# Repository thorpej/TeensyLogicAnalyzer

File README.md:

# TeensyLogicAnalyzer
Simple logic analyzer for 8-bit CPUs based on Jeff Tranter's 8-bit CPU logic analyzer

This is a work-in-progress.  You can find Jeff's work [here](https://github.com/jefftranter/6502).

This version aims to support a wide variety of 8-bit CPUs (so long as they fit in a 40-pin DIP)
and be easily expandable to new CPU types (e.g. 8080 and 8088) through the use of off-board adapter
modules, as well as to support sampling the full complement of control signals on the supported CPUs.

The main board is very similar to Jeff's original: it contains the Teensy 4.1, input buffers to
level-shift the 5V TTL signals from the target CPU down to the 3.3V levels supported by the Teensy,
a manual trigger button, and a ground reference pin (as a convenience).

The main difference is the use of a single keyed 40-pin IDC header.  This header's pinout does not
correspond directly to any single CPU type, but merely provides the input to the analyzer.
Individual adapter modules mate the analyzer to a specific CPU.  These adapter modules also contain
a 40-pin keyed IDC header, as well as 2 (optionally 3) rows of 1x20 pin headers for connecting a 40-pin
DIP clip to the adapter.  The adapter maps the target CPU's pin configuration to the analyzer's input
pins.  In addition to providing future expandability, it also keeps the manufacturing cost of the boards
low (some PCB fabricators charge as little as $5 + shipping for a run of 10 if the board is smaller
than 100mm x 100mm).  The analyzer board is approximately 91mm x 91mm (roughly 3.5 inches square), and
uses all through-hole components to make it easy to build.

In addition, I plan to make some specific enhancements to the 6809 support, including:
- Support additional signals on the 6809 (e.g. BS, BA, /FIRQ, /HALT).
- Properly notice instruction fetch on 6809E (by watching the LIC signal).
- Improve 6809 dissasembly (decode all of the addressing modes, as well as the 2-byte opcodes).

Beause the 6809E enhancements I want to make require additional signals to be routed, I needed
to make a new board anyway, which is why this project exists.

More to come.  Stay tuned!

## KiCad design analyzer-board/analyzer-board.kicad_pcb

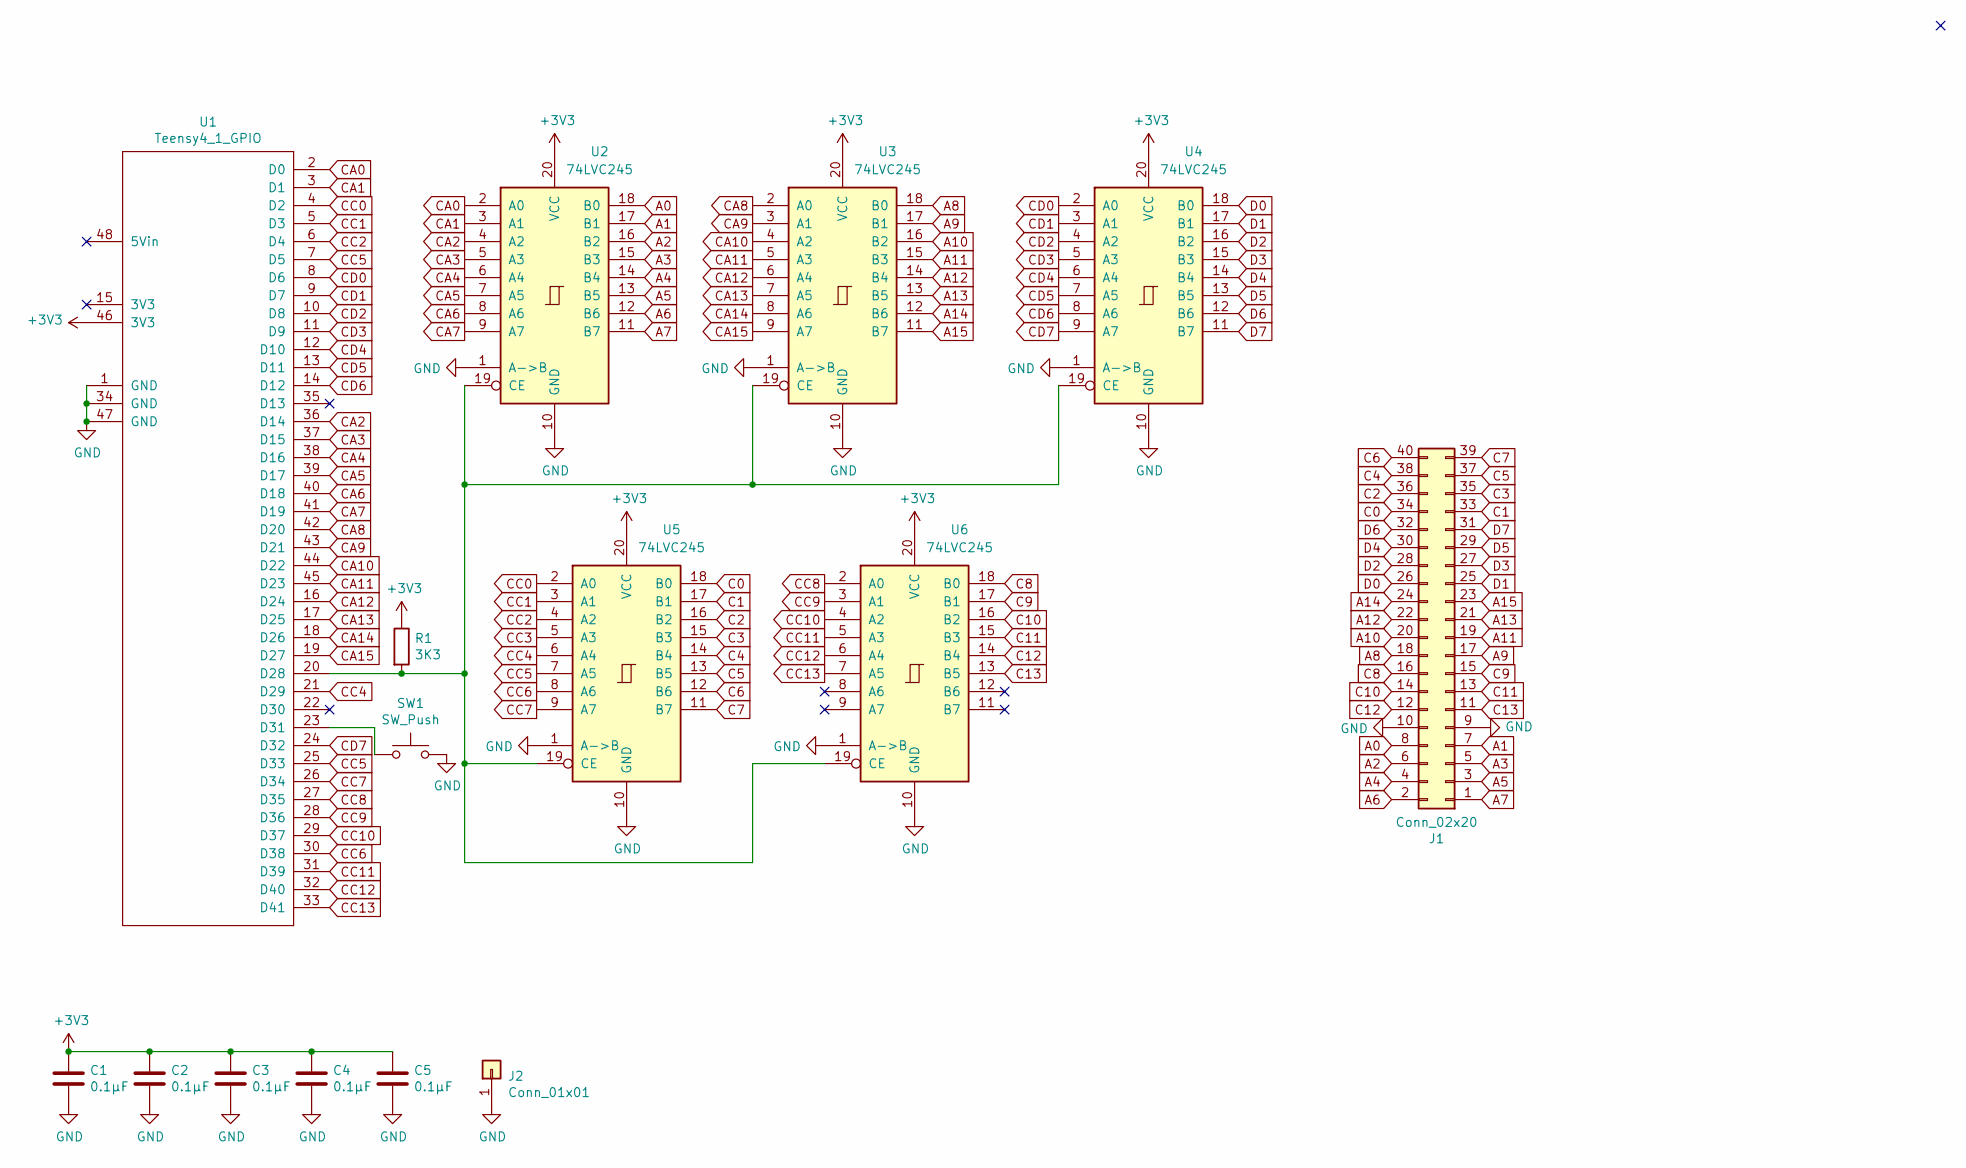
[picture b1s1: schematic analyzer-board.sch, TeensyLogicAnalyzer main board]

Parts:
C1, C2, C3, C4, C5: 0.1µF; C_Radial_D6.3mm_H5.0mm_P2.50mm; Mouser 80-C320C104K2R5TA
J1: Conn_02x20; PinHeader_2x20_P2.54mm_Vertical
J2: Conn_01x01; PinHeader_1x01_P2.54mm_Vertical
R1: 3K3; R_Axial_DIN0207_L6.3mm_D2.5mm_P7.62mm_Horizontal
SW1: SW_Push; SW_PUSH_6mm
U1: Teensy4_1_GPIO; DIP-48_W15.24mm_Socket
U2, U3, U4, U5, U6: 74LVC245; DIP-20_W7.62mm_Socket

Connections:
+3V3: C1.1, C2.1, C3.1, C4.1, C5.1, R1.1, U1.46 (3V3), U2.20 (VCC), U3.20 (VCC), U4.20 (VCC), U5.20 (VCC), U6.20 (VCC)
A0: J1.8, U2.18 (B0)
A1: J1.7, U2.17 (B1)
A2: J1.6, U2.16 (B2)
A3: J1.5, U2.15 (B3)
A4: J1.4, U2.14 (B4)
A5: J1.3, U2.13 (B5)
A6: J1.2, U2.12 (B6)
A7: J1.1, U2.11 (B7)
A8: J1.18, U3.18 (B0)
A9: J1.17, U3.17 (B1)
A10: J1.20, U3.16 (B2)
A11: J1.19, U3.15 (B3)
A12: J1.22, U3.14 (B4)
A13: J1.21, U3.13 (B5)
A14: J1.24, U3.12 (B6)
A15: J1.23, U3.11 (B7)
C0: J1.34, U5.18 (B0)
C1: J1.33, U5.17 (B1)
C2: J1.36, U5.16 (B2)
C3: J1.35, U5.15 (B3)
C4: J1.38, U5.14 (B4)
C5: J1.37, U5.13 (B5)
C6: J1.40, U5.12 (B6)
C7: J1.39, U5.11 (B7)
C8: J1.16, U6.18 (B0)
C9: J1.15, U6.17 (B1)
C10: J1.14, U6.16 (B2)
C11: J1.13, U6.15 (B3)
C12: J1.12, U6.14 (B4)
C13: J1.11, U6.13 (B5)
CA0: U1.2 (D0), U2.2 (A0)
CA1: U1.3 (D1), U2.3 (A1)
CA2: U1.36 (D14), U2.4 (A2)
CA3: U1.37 (D15), U2.5 (A3)
CA4: U1.38 (D16), U2.6 (A4)
CA5: U1.39 (D17), U2.7 (A5)
CA6: U1.40 (D18), U2.8 (A6)
CA7: U1.41 (D19), U2.9 (A7)
CA8: U1.42 (D20), U3.2 (A0)
CA9: U1.43 (D21), U3.3 (A1)
CA10: U1.44 (D22), U3.4 (A2)
CA11: U1.45 (D23), U3.5 (A3)
CA12: U1.16 (D24), U3.6 (A4)
CA13: U1.17 (D25), U3.7 (A5)
CA14: U1.18 (D26), U3.8 (A6)
CA15: U1.19 (D27), U3.9 (A7)
CC0: U1.4 (D2), U5.2 (A0)
CC1: U1.5 (D3), U5.3 (A1)
CC2: U1.6 (D4), U5.4 (A2)
CC3: U5.5 (A3)
CC4: U1.21 (D29), U5.6 (A4)
CC5: U1.7 (D5), U1.25 (D33), U5.7 (A5)
CC6: U1.30 (D38), U5.8 (A6)
CC7: U1.26 (D34), U5.9 (A7)
CC8: U1.27 (D35), U6.2 (A0)
CC9: U1.28 (D36), U6.3 (A1)
CC10: U1.29 (D37), U6.4 (A2)
CC11: U1.31 (D39), U6.5 (A3)
CC12: U1.32 (D40), U6.6 (A4)
CC13: U1.33 (D41), U6.7 (A5)
CD0: U1.8 (D6), U4.2 (A0)
CD1: U1.9 (D7), U4.3 (A1)
CD2: U1.10 (D8), U4.4 (A2)
CD3: U1.11 (D9), U4.5 (A3)
CD4: U1.12 (D10), U4.6 (A4)
CD5: U1.13 (D11), U4.7 (A5)
CD6: U1.14 (D12), U4.8 (A6)
CD7: U1.24 (D32), U4.9 (A7)
D0: J1.26, U4.18 (B0)
D1: J1.25, U4.17 (B1)
D2: J1.28, U4.16 (B2)
D3: J1.27, U4.15 (B3)
D4: J1.30, U4.14 (B4)
D5: J1.29, U4.13 (B5)
D6: J1.32, U4.12 (B6)
D7: J1.31, U4.11 (B7)
GND: C1.2, C2.2, C3.2, C4.2, C5.2, J1.9, J1.10, J2.1, SW1.2, U1.1 (GND), U1.34 (GND), U1.47 (GND), U2.1 (A->B), U2.10 (GND), U3.1 (A->B), U3.10 (GND), U4.1 (A->B), U4.10 (GND), U5.1 (A->B), U5.10 (GND), U6.1 (A->B), U6.10 (GND)
unnamed: R1.2, U1.20 (D28), U2.19 (CE), U3.19 (CE), U4.19 (CE), U5.19 (CE), U6.19 (CE)
unnamed: SW1.1, U1.23 (D31)

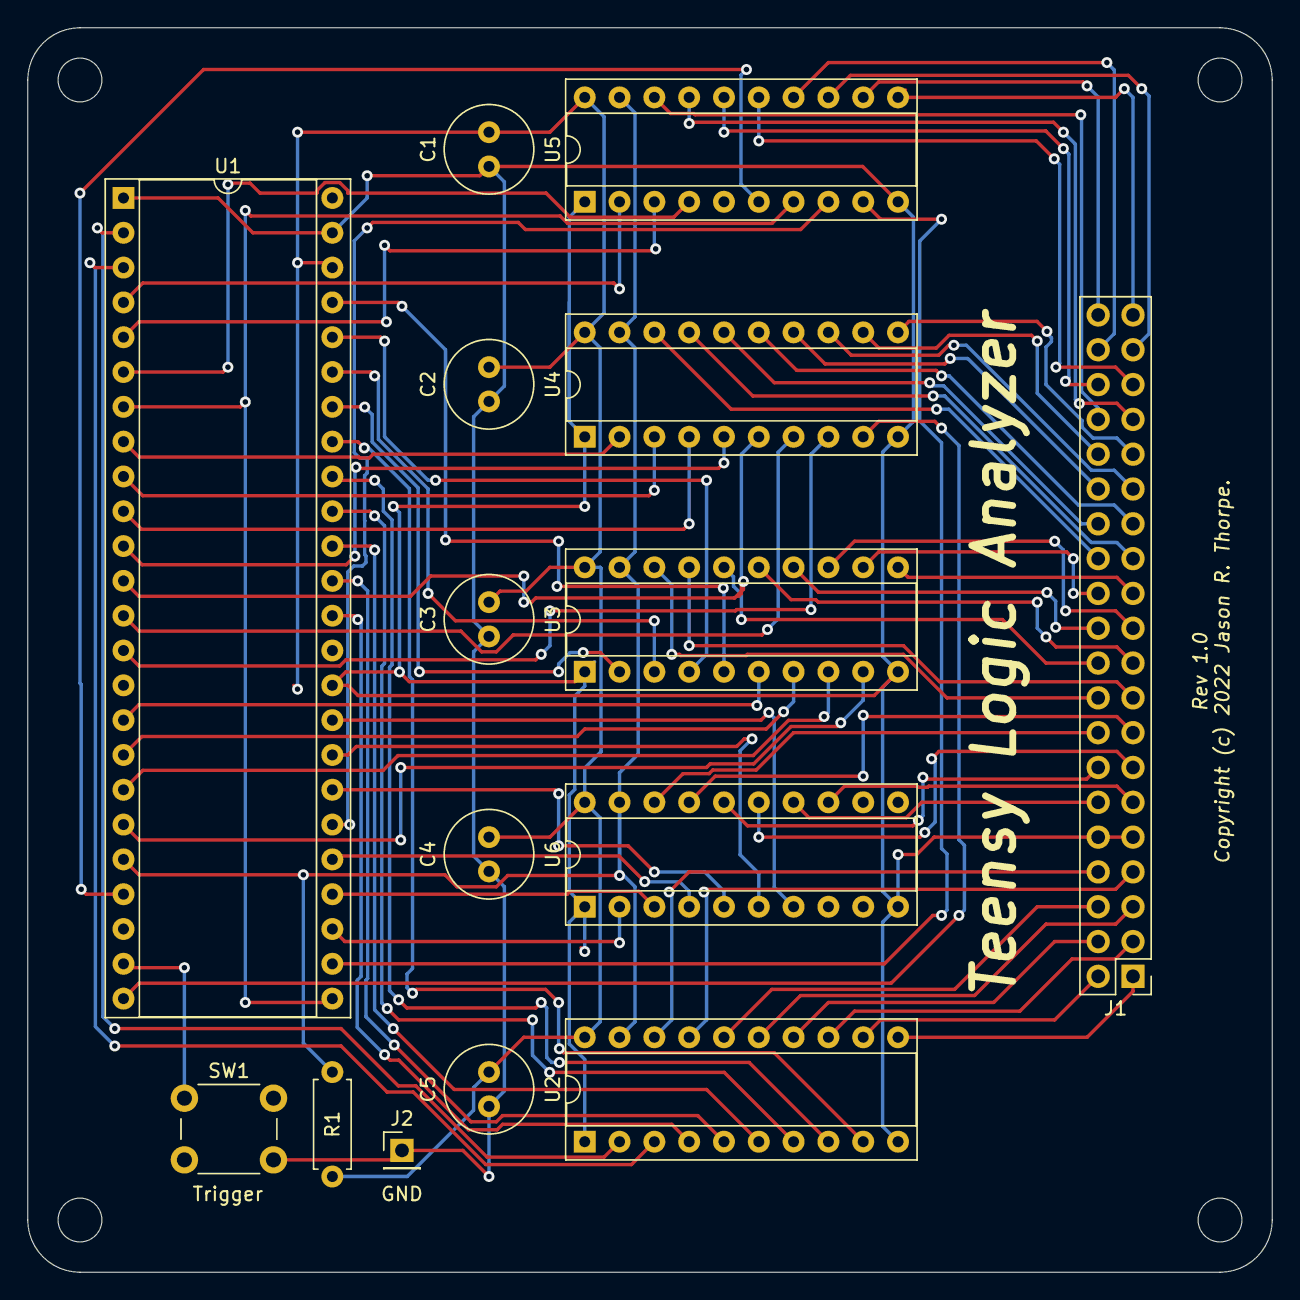
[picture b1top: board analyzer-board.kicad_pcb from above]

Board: 2 copper layers, 90.8 x 90.8 mm, 15 parts (0 on the bottom side), 79 nets.

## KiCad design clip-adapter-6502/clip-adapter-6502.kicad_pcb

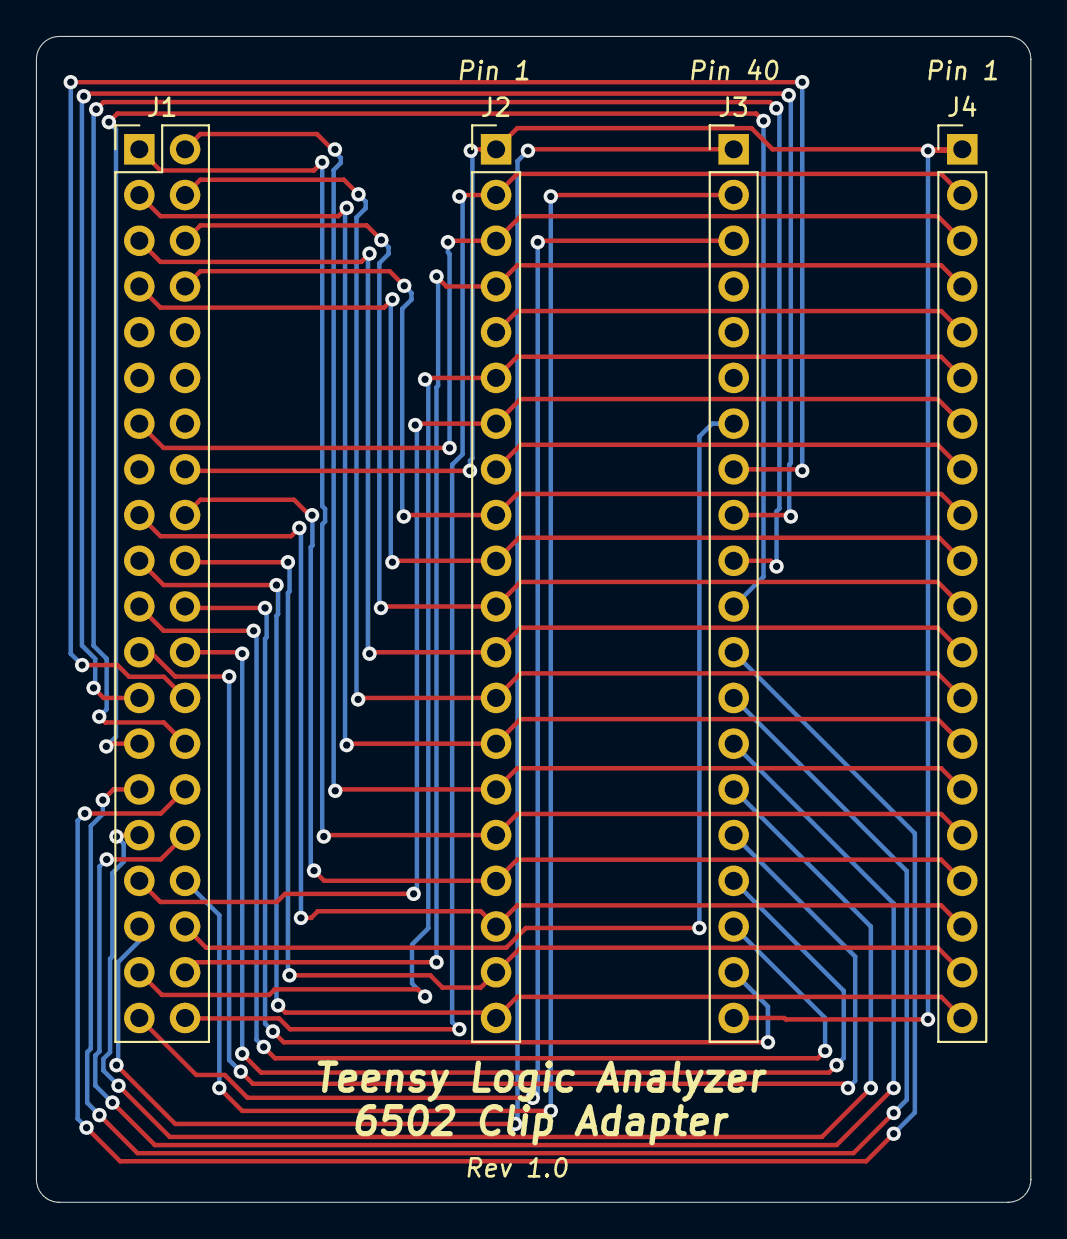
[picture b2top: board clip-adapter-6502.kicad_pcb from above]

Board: 2 copper layers, 55.2 x 64.8 mm, 4 parts (0 on the bottom side), 36 nets.

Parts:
J1: Conn_02x20; PinHeader_2x20_P2.54mm_Vertical
J2, J3, J4: Conn_01x20; PinHeader_1x20_P2.54mm_Vertical

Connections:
A0: J1.8, J2.9, J4.9
A1: J1.7, J2.10, J4.10
A2: J1.6, J2.11, J4.11
A3: J1.5, J2.12, J4.12
A4: J1.4, J2.13, J4.13
A5: J1.3, J2.14, J4.14
A6: J1.2, J2.15, J4.15
A7: J1.1, J2.16, J4.16
A8: J1.18, J2.17, J4.17
A9: J1.17, J2.18, J4.18
A10: J1.20, J2.19, J4.19
A11: J1.19, J2.20, J4.20
A12: J1.22, J3.19
A13: J1.21, J3.18
A14: J1.24, J3.17
A15: J1.23, J3.16
C0: J1.34, J3.2
C1: J1.33, J2.7, J4.7
C2: J1.36, J3.7
C3: J1.35, J3.1
C4: J1.38, J2.4, J4.4
C5: J1.37, J2.6, J4.6
C6: J1.40, J2.2, J4.2
C7: J1.39, J3.3
C10: J1.9, J1.10, J1.11, J1.12, J1.14, J1.15, J1.16, J2.1, J3.20, J4.1
C11: J1.13, J2.3, J4.3
D0: J1.26, J3.8
D1: J1.25, J3.9
D2: J1.28, J3.10
D3: J1.27, J3.11
D4: J1.30, J3.12
D5: J1.29, J3.13
D6: J1.32, J3.14
D7: J1.31, J3.15
unnamed: J2.5, J4.5
unnamed: J2.8, J4.8

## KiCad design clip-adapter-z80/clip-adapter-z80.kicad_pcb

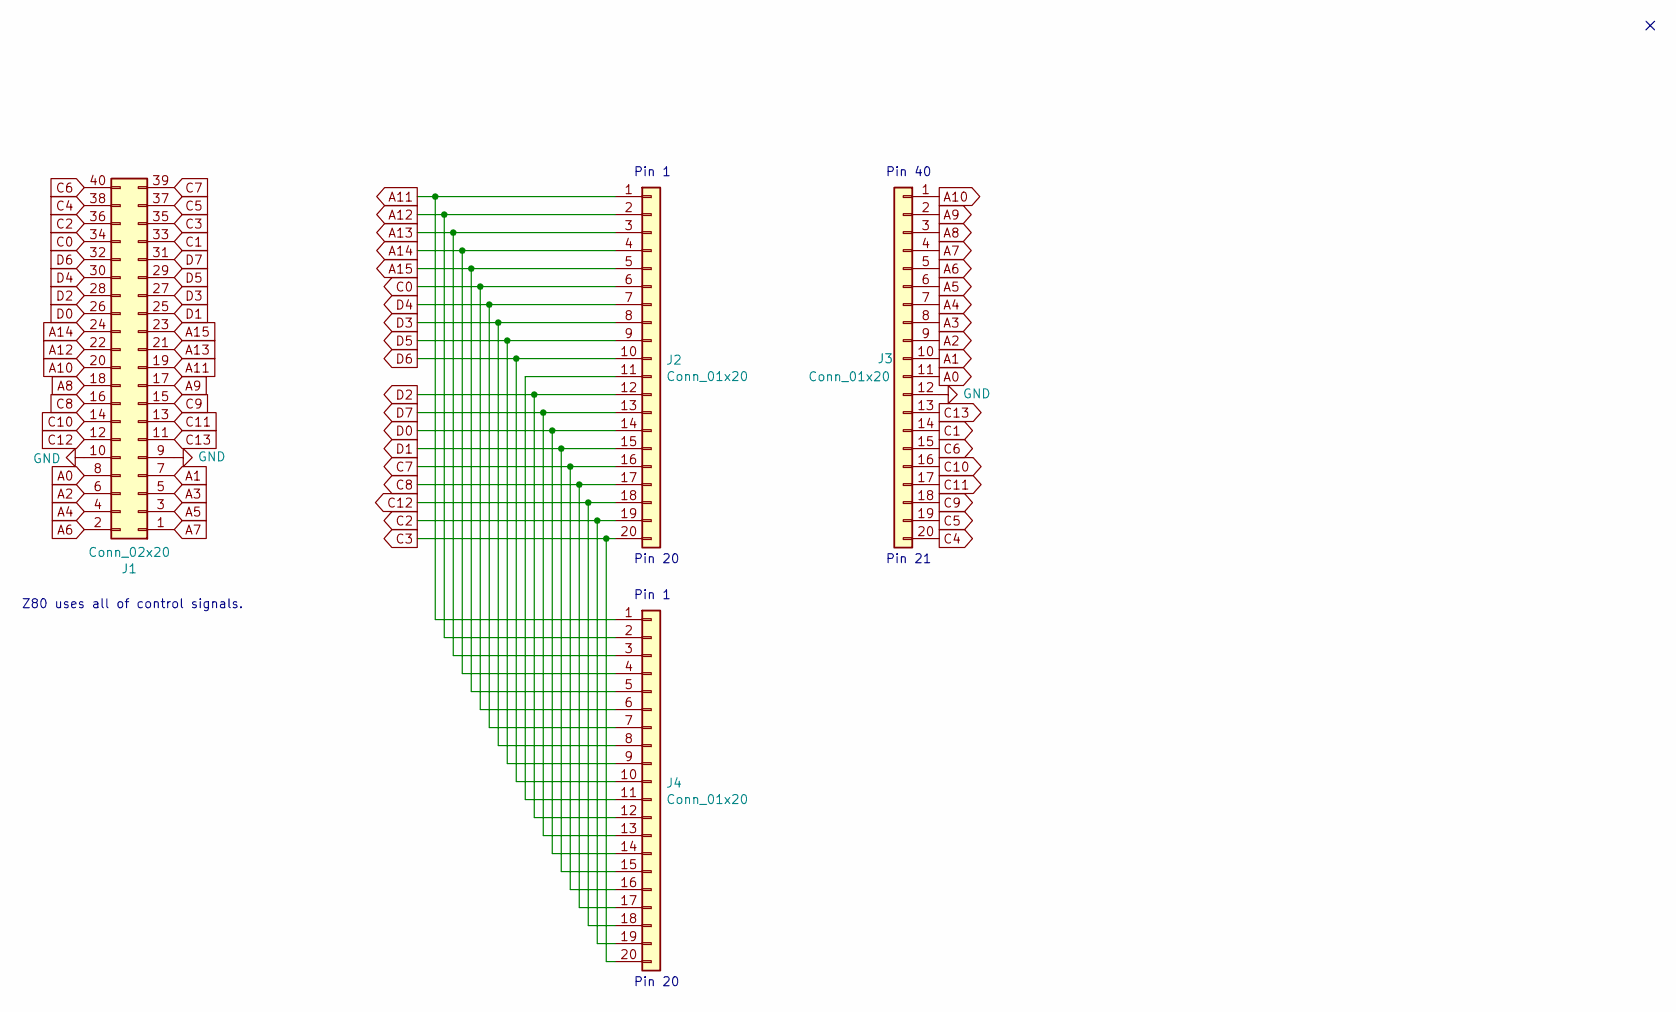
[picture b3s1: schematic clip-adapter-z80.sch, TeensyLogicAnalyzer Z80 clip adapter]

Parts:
J1: Conn_02x20; PinHeader_2x20_P2.54mm_Vertical
J2, J3, J4: Conn_01x20; PinHeader_1x20_P2.54mm_Vertical

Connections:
A0: J1.8, J3.11
A1: J1.7, J3.10
A2: J1.6, J3.9
A3: J1.5, J3.8
A4: J1.4, J3.7
A5: J1.3, J3.6
A6: J1.2, J3.5
A7: J1.1, J3.4
A8: J1.18, J3.3
A9: J1.17, J3.2
A10: J1.20, J3.1
A11: J1.19, J2.1, J4.1
A12: J1.22, J2.2, J4.2
A13: J1.21, J2.3, J4.3
A14: J1.24, J2.4, J4.4
A15: J1.23, J2.5, J4.5
C0: J1.34, J2.6, J4.6
C1: J1.33, J3.14
C2: J1.36, J2.19, J4.19
C3: J1.35, J2.20, J4.20
C4: J1.38, J3.20
C5: J1.37, J3.19
C6: J1.40, J3.15
C7: J1.39, J2.16, J4.16
C8: J1.16, J2.17, J4.17
C9: J1.15, J3.18
C10: J1.14, J3.16
C11: J1.13, J3.17
C12: J1.12, J2.18, J4.18
C13: J1.11, J3.13
D0: J1.26, J2.14, J4.14
D1: J1.25, J2.15, J4.15
D2: J1.28, J2.12, J4.12
D3: J1.27, J2.8, J4.8
D4: J1.30, J2.7, J4.7
D5: J1.29, J2.9, J4.9
D6: J1.32, J2.10, J4.10
D7: J1.31, J2.13, J4.13
GND: J1.9, J1.10, J3.12
unnamed: J2.11, J4.11

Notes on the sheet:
Pin 1
Pin 20
Pin 21
Pin 40
Z80 uses all of control signals.

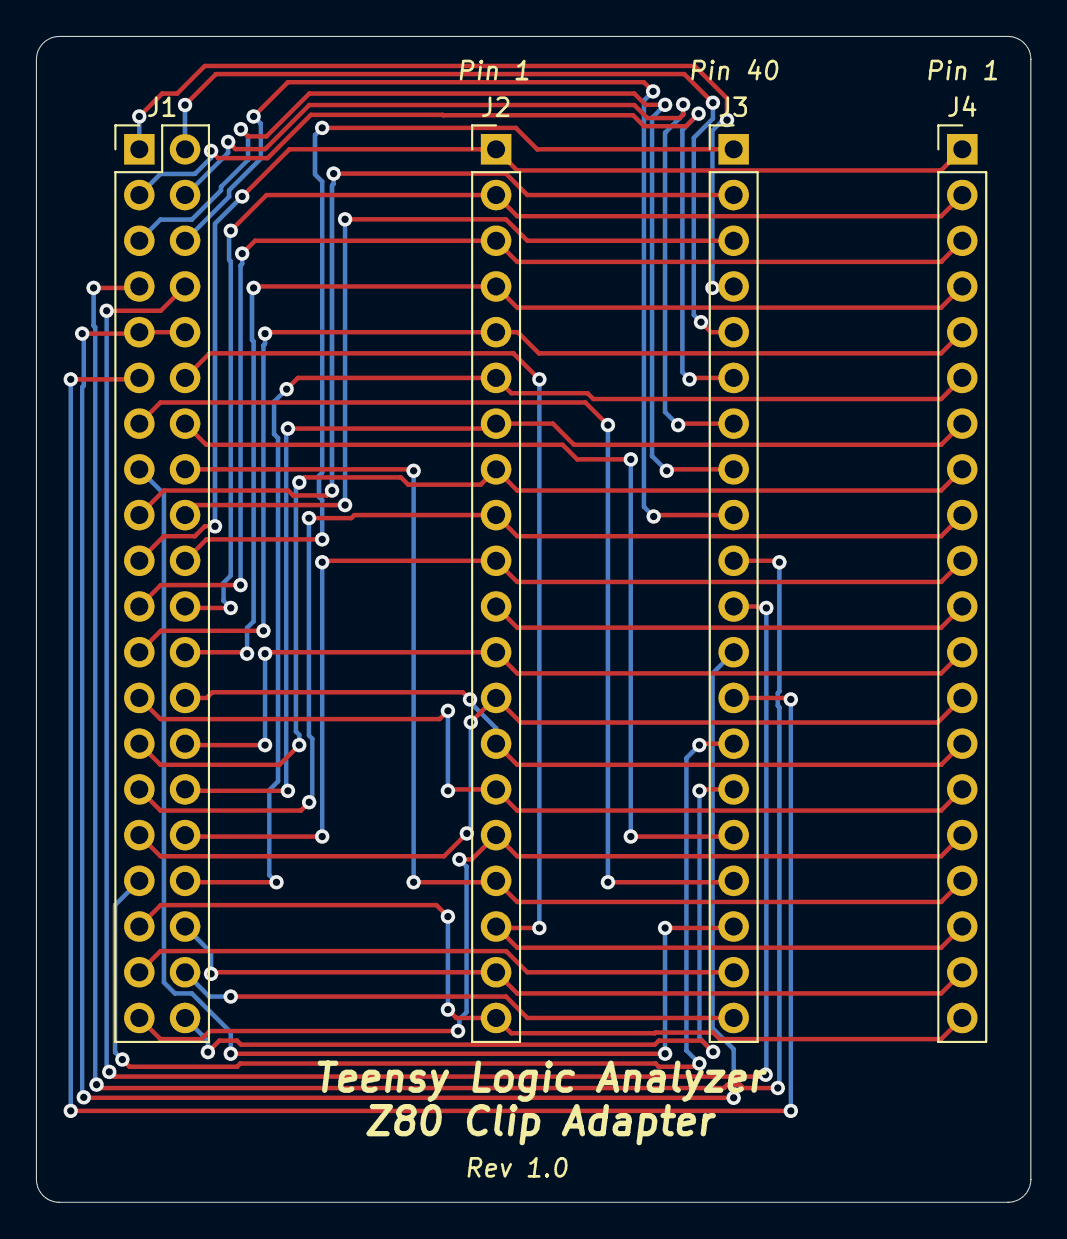
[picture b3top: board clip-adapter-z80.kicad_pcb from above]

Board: 2 copper layers, 55.2 x 64.8 mm, 4 parts (0 on the bottom side), 40 nets.

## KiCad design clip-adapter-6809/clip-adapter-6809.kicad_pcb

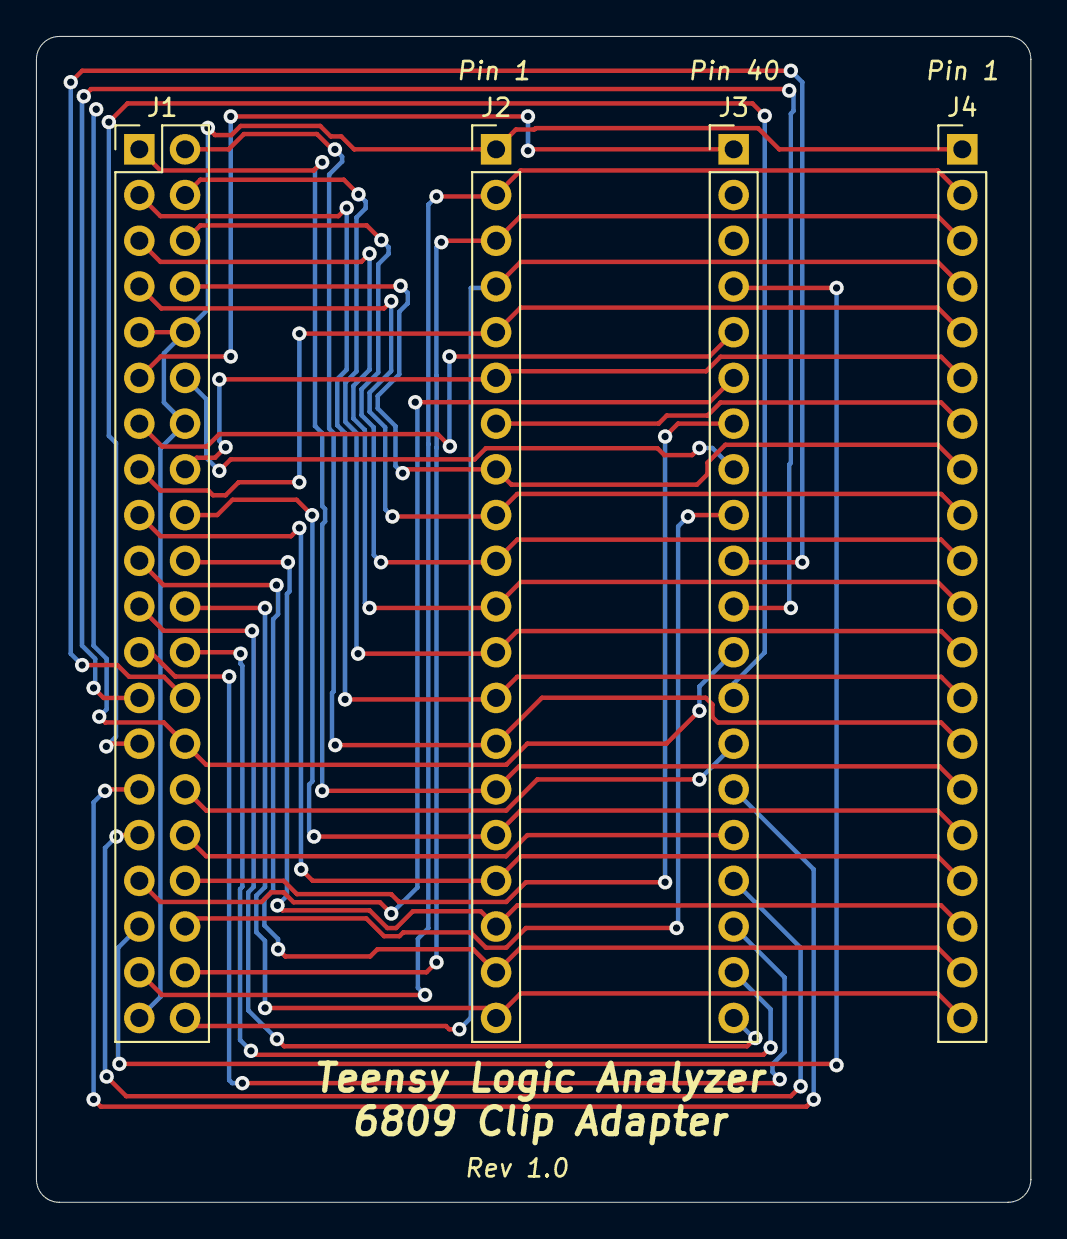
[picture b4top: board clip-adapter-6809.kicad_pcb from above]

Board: 2 copper layers, 55.2 x 64.8 mm, 4 parts (0 on the bottom side), 38 nets.

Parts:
J1: Conn_02x20; PinHeader_2x20_P2.54mm_Vertical
J2, J3, J4: Conn_01x20; PinHeader_1x20_P2.54mm_Vertical

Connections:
A0: J1.8, J2.8, J4.8
A1: J1.7, J2.9, J4.9
A2: J1.6, J2.10, J4.10
A3: J1.5, J2.11, J4.11
A4: J1.4, J2.12, J4.12
A5: J1.3, J2.13, J4.13
A6: J1.2, J2.14, J4.14
A7: J1.1, J2.15, J4.15
A8: J1.18, J2.16, J4.16
A9: J1.17, J2.17, J4.17
A10: J1.20, J2.18, J4.18
A11: J1.19, J2.19, J4.19
A12: J1.22, J2.20, J4.20
A13: J1.21, J3.20
A14: J1.24, J3.19
A15: J1.23, J3.18
C0: J1.34, J3.7
C1: J1.33, J3.6
C2: J1.36, J3.9
C3: J1.35, J3.4
C4: J1.38, J2.3, J4.3
C5: J1.37, J2.2, J4.2
C6: J1.40, J2.4, J4.4
C8: J1.16, J2.6, J4.6
C9: J1.15, J2.5, J4.5
C10: J1.9, J1.10, J1.14, J1.39, J2.1, J4.1
C11: J1.13, J3.5
C12: J1.12, J3.8
C13: J1.11, J3.1
D0: J1.26, J3.10
D1: J1.25, J3.11
D2: J1.28, J3.12
D3: J1.27, J3.13
D4: J1.30, J3.14
D5: J1.29, J3.15
D6: J1.32, J3.16
D7: J1.31, J3.17
unnamed: J2.7, J4.7

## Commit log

2022-04-22 Update README.md
    Initial (brief) description of the project.
2022-04-22 Initial commit of Jeff Tranter's LogicAnalyzer.ino, commit dbd79ea8748ecda5a6ee44c0c0312ede6dc9f7bb.
2022-04-23 Major cleanup of signal inputs: - Keep a master list of pins that are in-use on the Teensy 4.1 board, and reference which GPIO port they're part of. - Define macros for the A0-15 D0-7 and Cx inputs i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
2022-04-23 Remove the cpu_6800like* macros I ended up not using.
2022-04-23 Use the abtract Cxxx_PSR macros rather than referencing GPIOn_PSR directly.
2022-04-23 Different enough now to have it's own version string and TODO list. Also, remove some redundant definitions.
2022-04-23 Assign pins and functions to CC8 and CC9.
2022-04-23 Remove some unnecessary pin definitions.
2022-04-23 Add trigger-on-/FIRQ for 6809 CPUs.
2022-04-23 Add firq to the help. Remove spare trigger from the help.
2022-04-23 Allow /NMI triggers on Z80 now that it has its own control signal line.
2022-04-23 Add a separate 6809E cpu type.
2022-04-23 Use the abstract signal names in exportCSV().
2022-04-23 Emit /FIRQ into the CSV file for 6809.
2022-04-23 Emit BA and BS into the CSV file for 6809.
2022-04-23 Emit LIC into the CSV file for 6809E.
2022-04-23 In list(), use symbolic constants for the control signals, and add FIRQ in the 6809 case.
2022-04-23 Detect /VMA cycles on the 6809.
2022-04-23 Use LIC on 6809E to detect insn fetch.
2022-04-23 Update TODOs.
2022-04-23 Define control signals CC10 - CC13. This gives us a total of 38 signals to snoop (16 address, 8 data, 14 control) which is enough for any 40-pin CPU (because 2 of the pins are Vcc and GND).
    Assign the following signals for the 6809E:
    CC10 -- TSC (tri-state control)
    CC11 -- AVMA (advance VMA)
    CC12 -- BUSY
    CC13 -- /HALT (this one is used by the CoCo floppy controller)
    We're not using these signals in software yet, but at least they'll
2022-04-23 Assign inputs for MRDY and DMA_BREQ on vanilla 6809.
2022-04-23 Assign CC_6502_RDY.
2022-04-23 Assign CC_6800_HALT, CC_6800_DBE, CC_6800_BA, CC_6800_TSC.
2022-04-24 Assign CC_Z80_BUSACK, CC_Z80_BUSRQ, CC_Z80_WAIT, CC_Z80_HALT, CC_Z80_RFSH.
2022-04-24 Add a TODO to somehow utilize all of the control signals, since we now capture all of them for each of the supported 40-pin CPUs.
2022-04-24 Add a comment about our 38 snooped signals.
2022-04-24 Assign CC_6502_SO, CC_6502_PHI1, and CC_6800_PHI1 for completeness. Define CC_6502_PHI1_PIN and CC_6800_PHI1_PIN in case we ever want to act on those clock signal transitions.
2022-04-24 Define D28 as a data bus enable pin, configured as an open-drain output. The /CE signals of the '245s will be connected to an external pull-up resistor to keep them high-Z until we're ready to actual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
2022-04-24 Set the bus enabled state before and after capture.
2022-04-24 Because some control signals are in the CDxx_PSR, we need to also read that register when we read the CCxx_PSR and CAxx_PSR. We must then mix the appropriate set of bits together to store as the data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
2022-04-29 This board is input-only, not bi-directional like Tranter's (it's not really compatible with how I've mixed additional control signals into the same GPIO ports as address and data lines).
2022-04-30 Update README.md
    Update description based on evolving design direction.
2022-04-30 Update README.md
    Analyzer board is final; update info about it.
2022-04-30 Don't use INPUT_PULLUP for the CA/CD/CC pins; the 74LVC245 has push-pull ouputs.
2022-05-01 Rev 1.0 design files for the analyzer main board and clip adapter boards for 6502, 6800, 6809, 6809E, and Z80.
2022-05-01 Fix PCB revision -- it's 1.0.
2022-05-01 Add analyzer main board images.
2022-05-01 Add 6502 clip adapter images.
2022-05-01 Add 6800 clip adapter images.
2022-05-01 Add 6809 clip adapter images.
2022-05-01 Add 6809E clip adapter images.
2022-05-01 Add Z80 clip adapter images.
2022-05-01 Add Gerber files.
2022-05-01 Annotate 6809 insns with addressing modes.
2022-05-02 Refactor the 6502 dissassembly out of the main list() loop.
2022-05-03 Switch to a new state-machine instruction decoder. Just implemented for 6809E so far. 6502 and Z80 coming next. 6800 is left out in the cold (no first-cycle indicator).
2022-05-03 Record the address where insn decode begins.
2022-05-03 Compute the resolved address for PC-relative operations.
2022-05-03 Add helpers for reading 16-bit values from memory buffers.
2022-05-03 Add 6502 / 65C02 addressing modes.
2022-05-03 Visual cleanup for 6809 opcode tables.
2022-05-04 Convert the 6502 insn decode to the new style. This mostly works the way Tranter's original does, except with the stateful collection of insn bytes (avoids errors at the ring buffer boundary conditio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
2022-05-04 Actually wire in the 6502 decoder.
2022-05-04 Remove unneeded macro. Tweak detection of am6809_extended_ind.
2022-05-05 Re-factor the exportCSV() function; break out individual CPU cases into their own functions.
2022-05-05 Default cpu type to "none". Add commands to show current CPU, sample and pre-trigger sample count, and trigger.
2022-05-05 If no samples have been taken, don't show the sample data (and don't overwrite good sample data on the SD card with empty samples data).
2022-05-05 Better 6809 disassembly has been achieved.
2022-05-05 Remove some redundant assignments.
2022-05-05 Add a hook for specifying fake samples for debugging. Enabled at compile time only; normally, this will be disabled. Add a bunch of fake samples for 6809E that, while not being cycle-accurate in any 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
2022-05-06 Add 6502 debug sample data to exercise the instruction decoder.
2022-05-09 Fix a few bugs in the new insn decoder: - read_u16be() had a typo that caused an out-of-bounds memory access. - Fix 6502 / 65c02 relative addressing mode templates. - Fix visual alignment of am6502_r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
2022-05-09 Duh, don't check in DEBUG_6809.
2022-05-09 When print "*" as the cycle type for insn fetch continuations.
2022-05-09 Print the resolved PC-relative address, if computed.
2022-05-09 Remove an unnecessary optimization that messes with proper reporting of > 2 byte insn fetch.
2022-05-09 Fix decoding the A register in the accumulator-offset indexed mode for 6809, and correct a typo in the test cases for tha mode.
2022-05-09 Mask off unwanted bits when extracting 5-bit constant offset.
2022-05-09 Fix some opcode errors in the test cases.
2022-05-09 - Fix some 65c02 addressing modes. - in writeSD(), be verbose if cpu type isn't set.
2022-05-09 Test cases for 6809 TFR, EXG, PSH, PUL.
2022-05-09 Fix typo.
2022-05-09 Improve display of trigger / comments.
2022-05-10 Include the "Reserved" vector on 6809, too.
2022-05-10 Add the cycle-by-cycle flow examples from the 6809E data sheet to the test samples.
2022-05-10 Add synthetic trigger support for the synthetic test data.
2022-05-11 Indicate the trigger point in the CSV output.
2022-05-11 Add a "d <address>" command to decode the instruction at the specified address. Could be especially useful for CPUs where we don't have a signal telling us when instruction fetch begins (e.g. 6800, v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
2022-05-11 Allow insn decode state transition from compete -> fetching, and simplify the "d" command implementation slightly as a result.
2022-05-11 Implement 6800 instruction decoding.
2022-05-14 Checkpoint the new Z80 instruction decoder.
2022-05-14 Fix the pcrel operand type in z80_operand_types[].
2022-05-14 Z80 instruction decode checkpoint: should all be there now.
2022-05-14 Don't use a magic number of tbuf size.
2022-05-14 Make the fake debug data a little less verbose.
2022-05-14 - Fix a bug in cursor advancement in z80_next_operand(). - Add Z80 debug data for the 8-bit load group.
2022-05-14 D'oh, z80_next_operand() should iterate through the template, not the list of operand types.
2022-05-14 Fix a couple of comments.
2022-05-15 - Add test vectors for the 16-bit LD group. - Fix a bug in z80_hl_to_index() that caused "LD (XXXXh),IX" to be decoded incorrectly.
2022-05-15 Test vectors for the block instructions.
2022-05-15 - Add a bunch of additional test vectors for Z80, covering all of the remaining instruction decoder cases. - Fix a think-o in the last commit to z80_hl_to_index(). - In insn_decode_format_z80(), don'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
2022-05-15 Don't define DEBUG_Z80.
2022-05-15 Remove an incorrect comment.
2022-05-15 Add support for memory (address, data) cycle triggers on Z80.
2022-05-15 Add support for I/O address triggers on Z80.
2022-05-15 Help display improvements.
2022-05-15 Don't use a single variable for tigger address and data; separate them out. This will allow us to add more specific triggers like:
    trigger when data 0xa5 is read from address 0xdead
2022-05-15 Add support for "address and data" triggers, e.g.:
    tr ad DEAD A5 r
    ...will trigger when the data 0xa5 is read from address 0xdead.
2022-05-16 Separate out the trigger address from the space (mem or io).
2022-05-16 Fix a mistake in 6809E LIC handling: An opcode fetch has started /only/ when we observe LIC transitioning from high to low. So, don't consider an LIC seen on the last sample if LIC is still set on th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
2022-05-17 Refactor the test sample data into its own header file.
2022-05-17 Re-factor the instruction decode generic definitions into their own header file.
2022-05-17 Re-factor out the 6502 insn decoder into its own file.
2022-05-17 Re-factor the 6800 insn decoder into its own file.
2022-05-17 Re-factor Z80 instruction decoding into its own file.
2022-05-17 Re-factor the 6809 instruction decode into its own file.
2022-05-17 Re-factor the generic instruction decode logic into its own file.
2022-05-17 Hide some symbols not meant to be exposed.
2022-05-17 Refactor the code that parses address / data triggers.
2022-05-17 Condense a bunch of the Serial.print*() calls into an easier-to-use tla_printf().
2022-05-17 Put __format__ attribute on the tla_printf() prototype.
2022-05-17 Add a "t id" command, which is like "t ad", but uses the I/O space.
2022-05-18 Completely overhaul command processing. More complex, but also more forgiving about e.g. whitespace, better help, etc.
2022-05-18 Make tla_printf() work like normal printf(), and fix up several help messages.
2022-05-18 Allow prefix matching on commands. No need for short aliases.
2022-05-18 More improvements to the "trigger" command.
2022-05-18 Fix an instance of "hi" that should be "high".
2022-05-22 Make sure to configure the button pin as an INPUT_PULLUP.
2022-05-22 Make trigger mode "none" distinct from manual triggering. "manual" is now what "none" used to be (wait for button press), "none" now immediately begins gathering samples without waiting for any sort 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
2022-05-22 Bump to version 0.4.
2022-05-22 Fix a PCB error: The wrong footprint was used for the 6mm push button, causing the button input pin on the Teensy to be connected directly to ground. Fix this problem by using the correct footprint a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
    Bump schematic and PCB rev to 1.1.
2022-06-04 Correct resolved address calculation on 6809.

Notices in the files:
analyzer-board/analyzer-board.kicad_pcb:
Copyright (c) 2022 Jason R. Thorpe.  See LICENSE.
